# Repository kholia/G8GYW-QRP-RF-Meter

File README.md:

#### PCB Renderings

Note: The PCB design was validated on 28th-October-2022 - it works well over HF
range (1.8 MHz to 50 MHz).

This project uses the https://github.com/earlephilhower/arduino-pico core.

We have tuned the `curve fitting` to match that of `LUNARIS G6 HF VHF UHF SWR
METER` from `Ceda-Labz`.

Install this core in Arduino IDE, and then select `Generic RP2040` as the
target board.

Cost to build (in INR): Less than 1200 INR including the OLED screen, and PCB
from JLPCB.

#### Build Notes

- Calibration of every build can potentially differ.

#### BOM + Sources

Download and open `ibom.html` in your local browser.

- https://robu.in/product/waveshare-rp2040-zero-raspberry-pi-mcu-with-presoldered-header/ (https://rarecomponents.com/ has it too)

- https://robu.in/product/0-96-inch-i2c-iic-oled-lcd-module-4pin-with-vcc-gnd-white/ (5v compatible with 3.3v I2C lines)

- https://www.electronicscomp.com/ (1206 SMD components, https://www.comkey.in/ and https://evelta.com are better sources)

- ST 1N5711 diodes (https://www.semikart.com/)

- BN-43-202 (https://www.semikart.com/)

- https://projectpoint.in/ (24 + 27 SWG winding wire, high quality jumpers)

- https://www.ktron.in/ (SMA edge connector)

#### References

- https://sites.google.com/site/lofturj/power-and-swr-meter

- https://g8gyw.github.io/ (upstream project, see the binocular toroid windings instructions here)

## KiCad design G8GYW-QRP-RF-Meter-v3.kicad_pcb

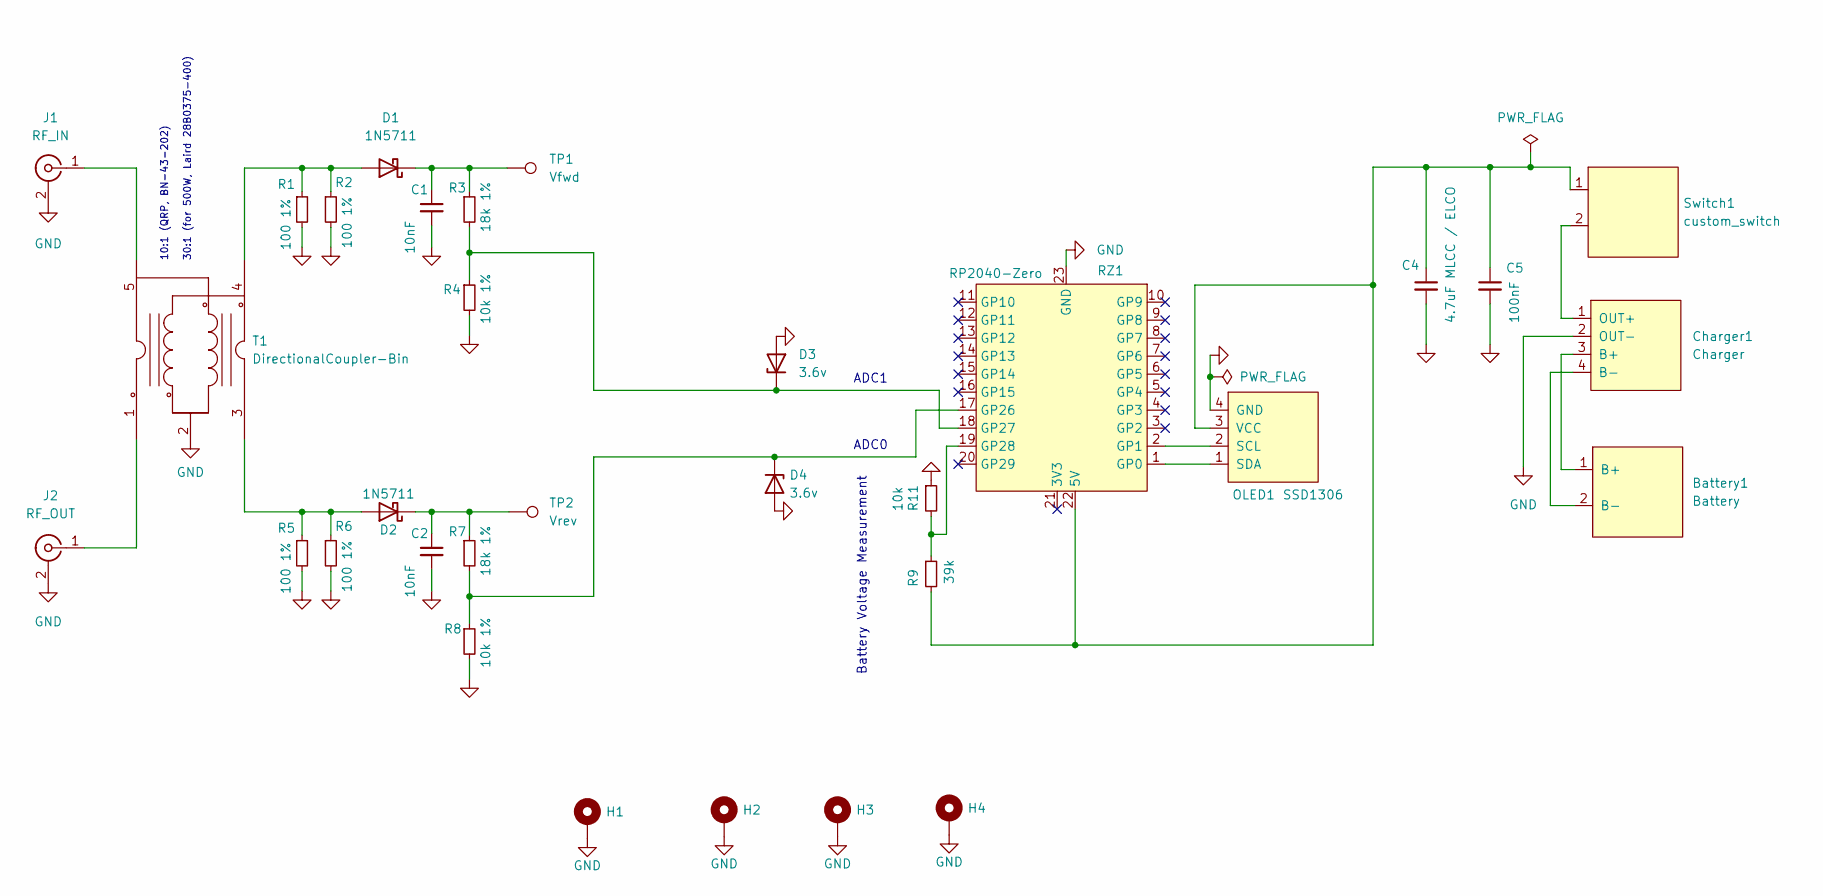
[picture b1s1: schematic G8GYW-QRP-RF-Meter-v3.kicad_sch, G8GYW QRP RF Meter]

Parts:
Battery1: Battery; PinHeader_1x02_P2.54mm_Vertical
C1, C2: 10nF; C_1206_3216Metric_Pad1.33x1.80mm_HandSolder
C4: 4.7uF MLCC / ELCO; C_1206_3216Metric_Pad1.33x1.80mm_HandSolder
C5: 100nF; C_1206_3216Metric_Pad1.33x1.80mm_HandSolder
Charger1: Charger; PinHeader_1x04_P2.54mm_Vertical
D1, D2: 1N5711; D_DO-35_SOD27_P2.54mm_Vertical_KathodeUp
D3, D4: 3.6v; D_DO-41_SOD81_P2.54mm_Vertical_KathodeUp
H1, H2, H3, H4: MountingHole_Pad; MountingHole_3.2mm_M3_ISO7380_Pad
J1: RF_IN; SMA_Samtec_SMA-J-P-X-ST-EM1_EdgeMount
J2: RF_OUT; SMA_Samtec_SMA-J-P-X-ST-EM1_EdgeMount
OLED1: SSD1306; PinHeader_1x04_P2.54mm_Vertical
R1, R2, R5, R6: 100 1%; R_1206_3216Metric_Pad1.30x1.75mm_HandSolder
R3, R7: 18k 1%; R_1206_3216Metric_Pad1.30x1.75mm_HandSolder
R4, R8: 10k 1%; R_1206_3216Metric_Pad1.30x1.75mm_HandSolder
R9: 39k; R_1206_3216Metric_Pad1.30x1.75mm_HandSolder
R11: 10k; R_1206_3216Metric_Pad1.30x1.75mm_HandSolder
RZ1: RP2040-Zero
Switch1: custom_switch; PinHeader_1x02_P2.54mm_Vertical
T1: DirectionalCoupler-Bin; BN-43-202-5P
TP1: Vfwd; PinHeader_1x01_P2.54mm_Vertical
TP2: Vrev; PinHeader_1x01_P2.54mm_Vertical

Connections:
GND: C1.2, C2.2, C4.2, C5.2, Charger1.2 (OUT-), D3.2 (A), D4.2 (A), H1.1, H2.1, H3.1, H4.1, J1.2 (Ext), J2.2 (Ext), OLED1.4 (GND), R1.2, R2.2, R4.2, R5.2, R6.2, R8.2, R11.1, RZ1.23 (GND), T1.2
unnamed: Battery1.1 (B+), Charger1.3 (B+)
unnamed: Battery1.2 (B-), Charger1.4 (B-)
unnamed: C1.1, D1.1 (K), R3.1, TP1.1
unnamed: C2.1, D2.1 (K), R7.1, TP2.1
unnamed: C4.1, C5.1, OLED1.3 (VCC), R9.2, RZ1.22 (5V), Switch1.1
unnamed: Charger1.1 (OUT+), Switch1.2
unnamed: D1.2 (A), R1.1, R2.1, T1.4
unnamed: D2.2 (A), R5.1, R6.1, T1.3
unnamed: D3.1 (K), R3.2, R4.1, RZ1.18 (GP27)
unnamed: D4.1 (K), R7.2, R8.1, RZ1.17 (GP26)
unnamed: J1.1 (In), T1.5
unnamed: J2.1 (In), T1.1
unnamed: OLED1.1 (SDA), RZ1.1 (GP0)
unnamed: OLED1.2 (SCL), RZ1.2 (GP1)
unnamed: R9.1, R11.2, RZ1.19 (GP28)

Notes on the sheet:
Battery Voltage Measurement
ADC0
ADC1
10:1 (QRP, BN-43-202) 30:1 (for 500W, Laird 28B0375-400)

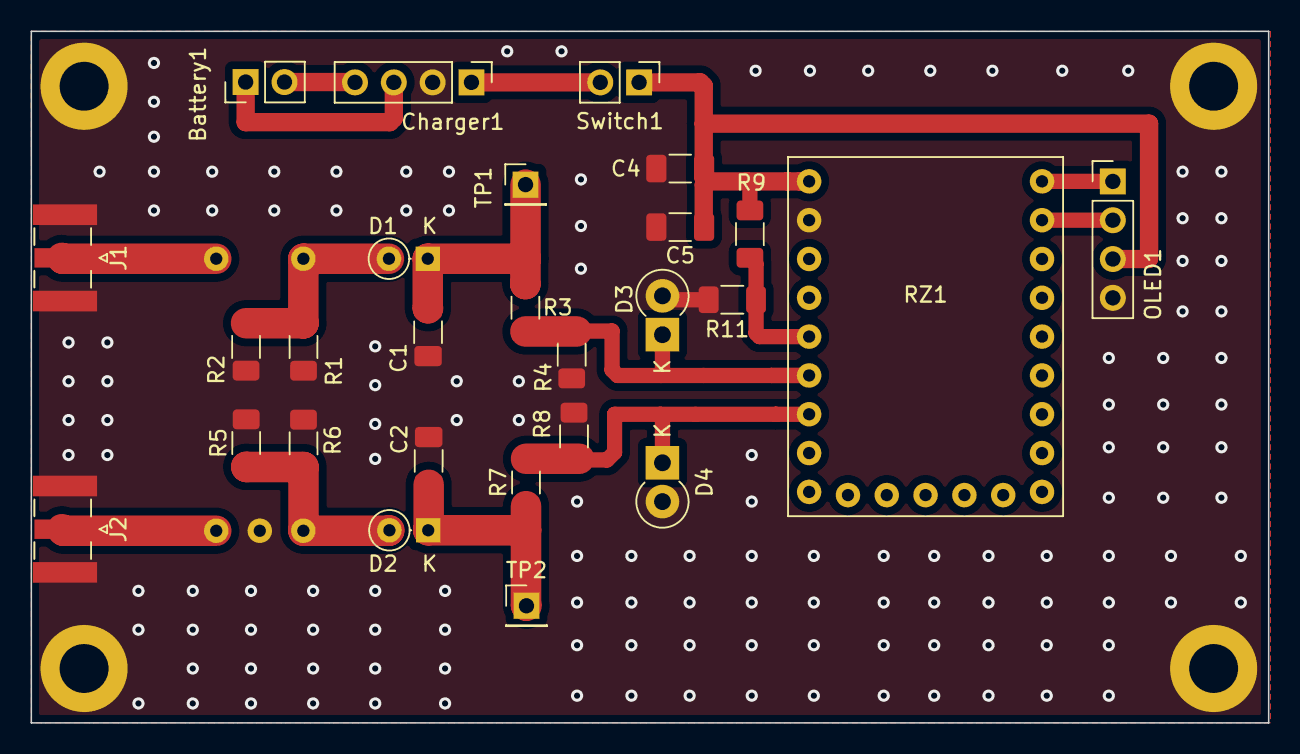
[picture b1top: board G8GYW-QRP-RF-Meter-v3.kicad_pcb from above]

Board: 2 copper layers, 81.0 x 45.3 mm, 32 parts (0 on the bottom side), 16 nets.

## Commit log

2022-06-28 Initial version
